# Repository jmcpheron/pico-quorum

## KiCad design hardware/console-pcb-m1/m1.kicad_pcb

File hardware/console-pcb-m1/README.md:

# M1 prototype console carrier

2026-10-07. Native KiCad schematic and routed PCB for the eight-button prototype.
The user chose an LCD module and a separate protected key adapter. The carrier
can now be quoted as a PCB assembly. It has not been built or bench-tested.

This version lives in `hardware/console-pcb-m1/`. Its CAD, local libraries,
fabrication exports and review drawings are kept together. Earlier concepts
remain in `hardware/console-pcb/`; they are separate versions.

- [Native schematic](m1.kicad_sch), [PCB](m1.kicad_pcb), [project](m1.kicad_pro).
- [Quote package](fab/m1-quote.zip), including Gerbers/drills, BOM, placement,
  schematic, assembly drawing, bare-board STEP, reports and file hashes.
- [Assembly and quote instructions](ASSEMBLY.md), including both harness pinouts.
- [Circuit drawing](review/m1.svg) and [placement drawing](review/placement.svg).

The carrier is 70 x 95 mm, two layers, with all 30 fitted parts on top. It has a
headerless Pico 2 W, eight SMT buttons, a JST PH LCD connector, 33R display series
resistors, local decoupling, host bus pull-ups, a default-off request pull-down,
four debug/service pads and eight internal key-adapter pads. Power comes from
the Pico's micro-USB socket. No battery or rotary control is included.

The display is Waveshare's 1.3inch LCD Module, SKU 15867, bought and mounted separately.
It uses a keyed harness rather than a soldered bare-panel ribbon. The adapter's
protection circuit is not on this board. Do not connect a USB-C plug or key directly
to the host pads. See ASSEMBLY.md for what that separate adapter must do.

The PCB's radio cutout and copper void follow the Pico module footprint. The main
board neck carries the traces around the antenna area. Keep the LCD, cable and
case hardware clear of that area. The screen envelope is an allowance: no enclosure
or complete assembly stack has been checked. The render uses the stock Pico W model
as a shape stand-in for Pico 2 W; the LCD and J1 connector body are not modelled.

## Checks completed

KiCad 10.0.6: ERC **0 errors / 0 warnings**; all-severity DRC **0 findings**;
unconnected items **0**; schematic/PCB parity **0**. No custom DRC exclusions were
added. The reports also list KiCad's default ignored checks. The export script
verifies that the 30 BOM references equal the placement references, and that all
are on the top side. Both checks passed.

Compared the Pico footprint, underside pads and stencil drawing with the maker's
PDF. Checked the switch's pad dimensions and internally common terminals. Checked
the JST PH family, pitch and header dimensions; the downloaded JST land-pattern
page could not be fully rendered because the local PDF reader lacks its font map.
The connector uses the stock KiCad footprint and still needs assembler drawing review.
Read the LCD's manual and circuit, including the backlight transistor and opposite
connector numbering. Inspected the exported schematic and PCB render.

Ran `git diff --check` and whitespace checks on new text files. Exported and checked
the Gerber/drill archive, BOM/CPL reference sets and file hashes. No firmware, web or
browser CI suites ran: this change is hardware CAD and supporting files only.
No installed dependency, board write, chip provisioning, lock, supplier quote or order.

Some local KiCad checks/rendering crashed in the filesystem sandbox. They completed
outside it. KiCad also logged a font-config notice; circuit/PCB checks completed.
PCB scripts use the existing key-board schematic helper and installed KiCad Python.
No dependency was added.

## Still to check

Assembler acceptance of the Pico module, stencil, JST footprint and parts sourcing;
LCD harness continuity and physical stack; button plungers and Sign recess; milled
cutout corner radii; Wi-Fi and supply behaviour under load; protected adapter design
and tests; Select/Device navigation and the existing review/reject/hold-to-sign checks.
Quote the carrier now, then resolve those before making or using a complete console.

`bootstrap.py` made the initial native files. It deliberately produces an unrouted
board and refuses to overwrite without `--force`. **Do not rerun it on this routed
design.** The native files are now the source. Regenerate exports with:

```sh
python3 hardware/console-pcb-m1/export.py
```

That command needs `kicad-cli`. STEP/rendering additionally use the installed KiCad
models. The `console_m1` symbol and footprint libraries are local to this project.
No change to the signing site, firmware image, ordered key-C board or release tags.

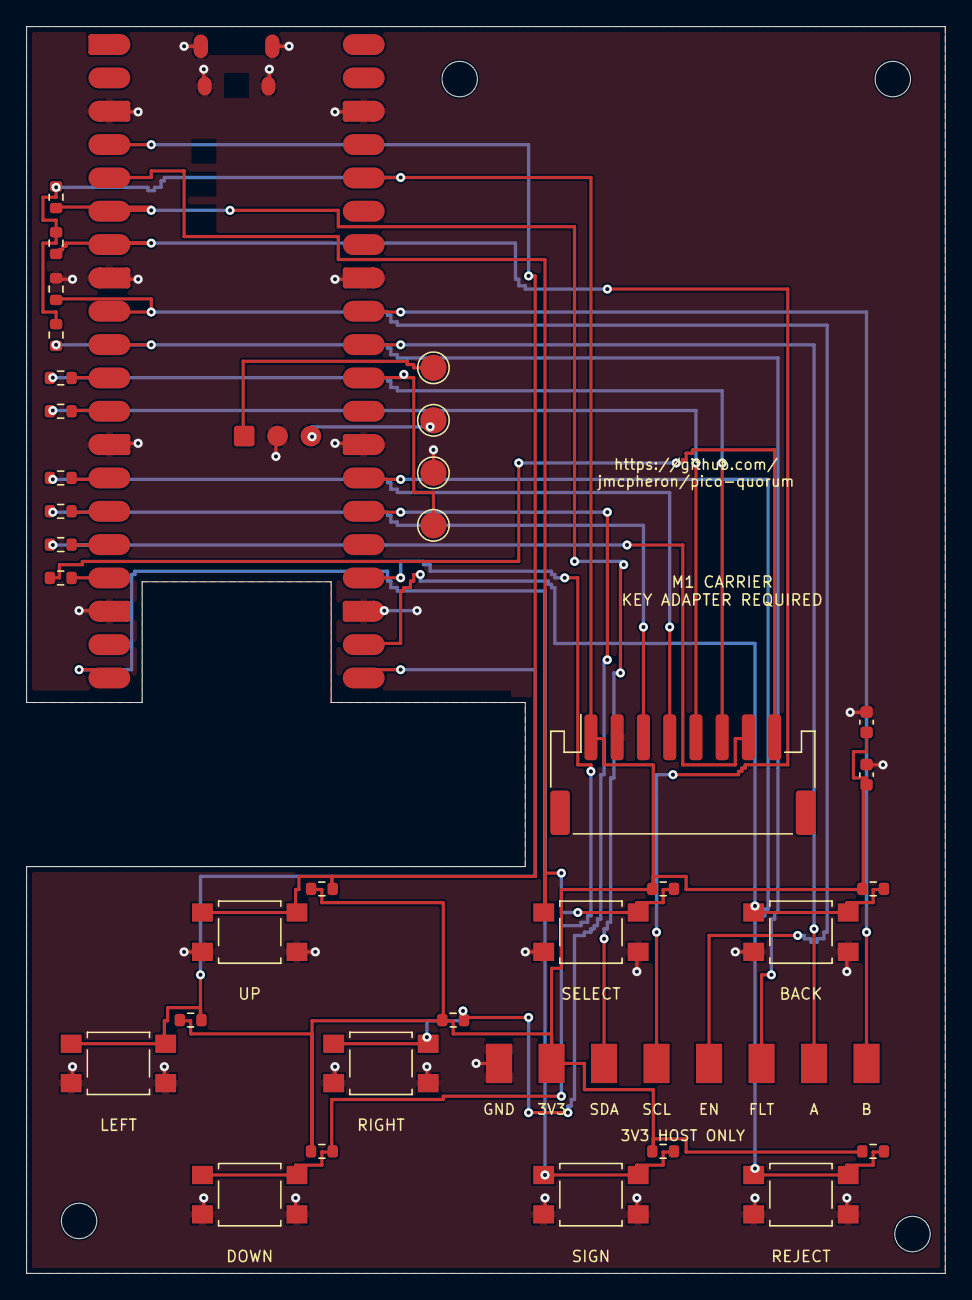
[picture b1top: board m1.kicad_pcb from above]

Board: 2 copper layers, 70.0 x 95.0 mm, 39 parts (0 on the bottom side), 31 nets.

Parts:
C1: 100n; C_0603_1608Metric
C2: 10u; C_0603_1608Metric
H1, H2, H3, H4: M2.5; MountingHole_2.7mm_M2.5
J1: S8B-PH-SM4-TB; JST_PH_S8B-PH-SM4-TB_1x08-1MP_P2.00mm_Horizontal
J2: INTERNAL ADAPTER PADS; AdapterPads8
R1, R2, R3, R4, R5, R6, R7, R8, R18: 10k; R_0603_1608Metric
R9, R10, R11, R12, R13, R14: 33R; R_0603_1608Metric
R15, R16: 2.2k; R_0603_1608Metric
R17: 100k; R_0603_1608Metric
SW1, SW2, SW3, SW4, SW5, SW6, SW7, SW8: TL3305AF160QG; SW_SPST_TL3305A
TP1: SWCLK; TestPoint_Pad_D2.0mm
TP2: SWDIO; TestPoint_Pad_D2.0mm
TP3: GND; TestPoint_Pad_D2.0mm
TP4: RUN; TestPoint_Pad_D2.0mm
U1: Pico 2 W; Pico2W_SMD

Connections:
/+3V3: C1.1, C2.1, J1.1, J2.2, R1.1, R2.1, R3.1, R4.1, R5.1, R6.1, R7.1, R8.1, R15.2, R16.2, R18.2, U1.36
/ATTACH_A: J2.7, U1.31
/ATTACH_B: J2.8, U1.32
/BTN_BACK: R6.2, SW6.1, U1.22
/BTN_DOWN: R2.2, SW2.1, U1.24
/BTN_LEFT: R3.2, SW3.1, U1.21
/BTN_REJECT: R8.2, SW8.1, U1.27
/BTN_RIGHT: R4.2, SW4.1, U1.26
/BTN_SELECT: R5.2, SW5.1, U1.5
/BTN_SIGN: R7.2, SW7.1, U1.20
/BTN_UP: R1.2, SW1.1, U1.4
/HOST_SCL: J2.4, R16.1, U1.7
/HOST_SDA: J2.3, R15.1, U1.6
/KEY_EN: J2.5, R17.1, U1.9
/KEY_FAULT: J2.6, R18.1, U1.10
/LCD_BL: J1.8, R14.2
/LCD_CS: J1.5, R11.2
/LCD_DC: J1.6, R12.2
/LCD_MOSI: J1.3, R9.2
/LCD_RST: J1.7, R13.2
/LCD_SCK: J1.4, R10.2
/MCU_BL: R14.1, U1.17
/MCU_CS: R11.1, U1.12
/MCU_DC: R12.1, U1.11
/MCU_MOSI: R9.1, U1.15
/MCU_RST: R13.1, U1.16
/MCU_SCK: R10.1, U1.14
/RUN: TP4.1, U1.30
/SWCLK: TP1.1, U1.D1
/SWDIO: TP2.1, U1.D3
GND: C1.2, C2.2, J1.2, J2.1, R17.2, SW1.2, SW2.2, SW3.2, SW4.2, SW5.2, SW6.2, SW7.2, SW8.2, TP3.1, U1.3, U1.8, U1.13, U1.18, U1.23, U1.28, U1.33, U1.38, U1.D2

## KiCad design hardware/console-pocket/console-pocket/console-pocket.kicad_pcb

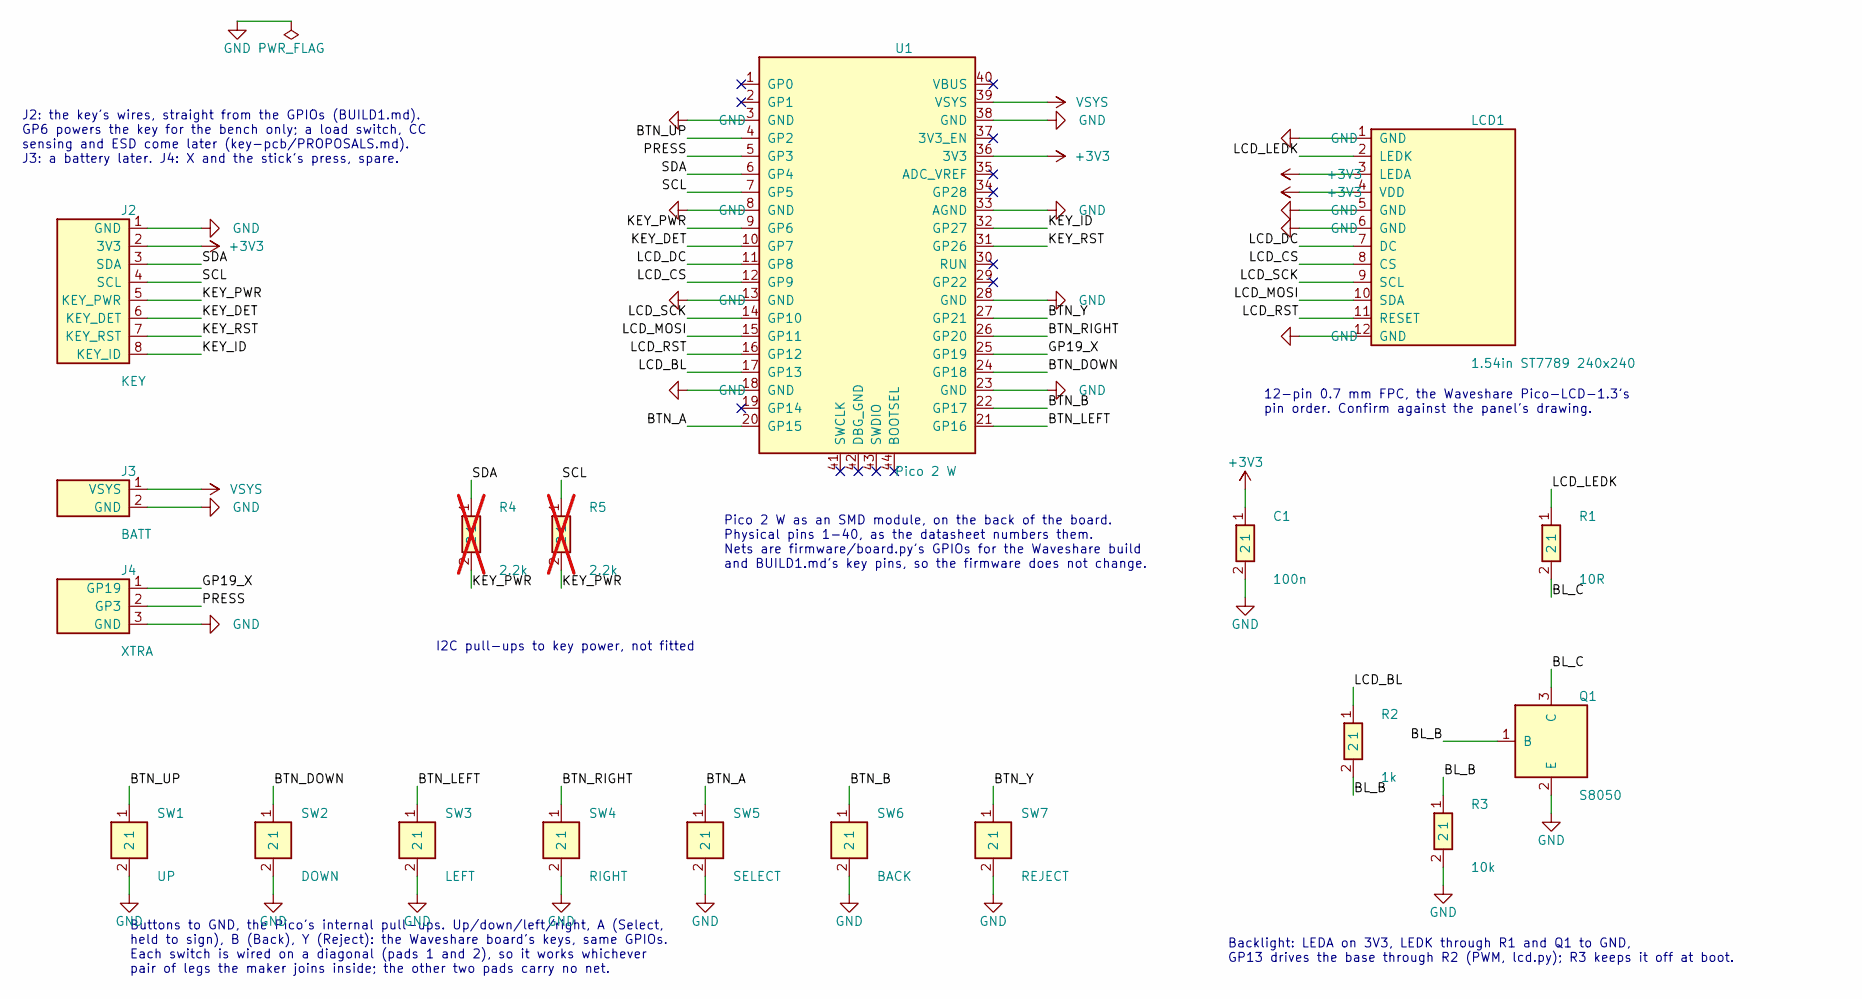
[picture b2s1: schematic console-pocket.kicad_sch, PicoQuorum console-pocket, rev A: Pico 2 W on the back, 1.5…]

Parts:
C1: 100n; C_0603; LCSC C14663
J2: KEY; Pads_1x8_P2.54mm
J3: BATT; Pads_1x2_P2.54mm
J4: XTRA; Pads_1x3_P2.54mm
LCD1: 1.54in ST7789 240x240; LCD_1.54in_240x240_FPC12_P0.7mm
Q1: S8050; SOT-23; MPN S8050 J3Y; LCSC C2150
R1: 10R; R_0603; LCSC C22859
R2: 1k; R_0603; LCSC C21190
R3: 10k; R_0603; LCSC C25804
R4, R5: 2.2k; R_0603; LCSC C4190; not fitted
SW1: UP; SW_SMD_6x6x5_TS1097A; MPN TS-1097A-05026; LCSC C720496
SW2: DOWN; SW_SMD_6x6x5_TS1097A; MPN TS-1097A-05026; LCSC C720496
SW3: LEFT; SW_SMD_6x6x5_TS1097A; MPN TS-1097A-05026; LCSC C720496
SW4: RIGHT; SW_SMD_6x6x5_TS1097A; MPN TS-1097A-05026; LCSC C720496
SW5: SELECT; SW_SMD_6x6x5_TS1097A; MPN TS-1097A-05026; LCSC C720496
SW6: BACK; SW_SMD_6x6x5_TS1097A; MPN TS-1097A-05026; LCSC C720496
SW7: REJECT; SW_SMD_6x6x5_TS1097A; MPN TS-1097A-05026; LCSC C720496
U1: Pico 2 W; Pico2W_SMD; MPN SC1633

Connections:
+3V3: C1.1, J2.2 (3V3), LCD1.3 (LEDA), LCD1.4 (VDD), U1.36 (3V3)
/BL_B: Q1.1 (B), R2.2, R3.1
/BL_C: Q1.3 (C), R1.2
/BTN_A: SW5.1, U1.20 (GP15)
/BTN_B: SW6.1, U1.22 (GP17)
/BTN_DOWN: SW2.1, U1.24 (GP18)
/BTN_LEFT: SW3.1, U1.21 (GP16)
/BTN_RIGHT: SW4.1, U1.26 (GP20)
/BTN_UP: SW1.1, U1.4 (GP2)
/BTN_Y: SW7.1, U1.27 (GP21)
/GP19_X: J4.1 (GP19), U1.25 (GP19)
/KEY_DET: J2.6 (KEY_DET), U1.10 (GP7)
/KEY_ID: J2.8 (KEY_ID), U1.32 (GP27)
/KEY_PWR: J2.5 (KEY_PWR), R4.2, R5.2, U1.9 (GP6)
/KEY_RST: J2.7 (KEY_RST), U1.31 (GP26)
/LCD_BL: R2.1, U1.17 (GP13)
/LCD_CS: LCD1.8 (CS), U1.12 (GP9)
/LCD_DC: LCD1.7 (DC), U1.11 (GP8)
/LCD_LEDK: LCD1.2 (LEDK), R1.1
/LCD_MOSI: LCD1.10 (SDA), U1.15 (GP11)
/LCD_RST: LCD1.11 (RESET), U1.16 (GP12)
/LCD_SCK: LCD1.9 (SCL), U1.14 (GP10)
/PRESS: J4.2 (GP3), U1.5 (GP3)
/SCL: J2.4 (SCL), R5.1, U1.7 (GP5)
/SDA: J2.3 (SDA), R4.1, U1.6 (GP4)
GND: C1.2, J2.1 (GND), J3.2 (GND), J4.3 (GND), LCD1.1 (GND), LCD1.5 (GND), LCD1.6 (GND), LCD1.12 (GND), Q1.2 (E), R3.2, SW1.2, SW2.2, SW3.2, SW4.2, SW5.2, SW6.2, SW7.2, U1.3 (GND), U1.8 (GND), U1.13 (GND), U1.18 (GND), U1.23 (GND), U1.28 (GND), U1.33 (AGND), U1.38 (GND)
VSYS: J3.1 (VSYS), U1.39 (VSYS)

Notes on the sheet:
Pico 2 W as an SMD module, on the back of the board. Physical pins 1-40, as the datasheet numbers them. Nets are firmware/board.py's GPIOs for the Waveshare build and BUILD1.md's key pins, so the firmware does not change.
Buttons to GND, the Pico's internal pull-ups. Up/down/left/right, A (Select, held to sign), B (Back), Y (Reject): the Waveshare board's keys, same GPIOs. Each switch is wired on a diagonal (pads 1 and 2), so it works whichever pair of legs the maker joins inside; the other two pads carry no net.
J2: the key's wires, straight from the GPIOs (BUILD1.md). GP6 powers the key for the bench only; a load switch, CC sensing and ESD come later (key-pcb/PROPOSALS.md). J3: a battery later. J4: X and the stick's press, spare.
I2C pull-ups to key power, not fitted
12-pin 0.7 mm FPC, the Waveshare Pico-LCD-1.3's pin order. Confirm against the panel's drawing.
Backlight: LEDA on 3V3, LEDK through R1 and Q1 to GND, GP13 drives the base through R2 (PWM, lcd.py); R3 keeps it off at boot.

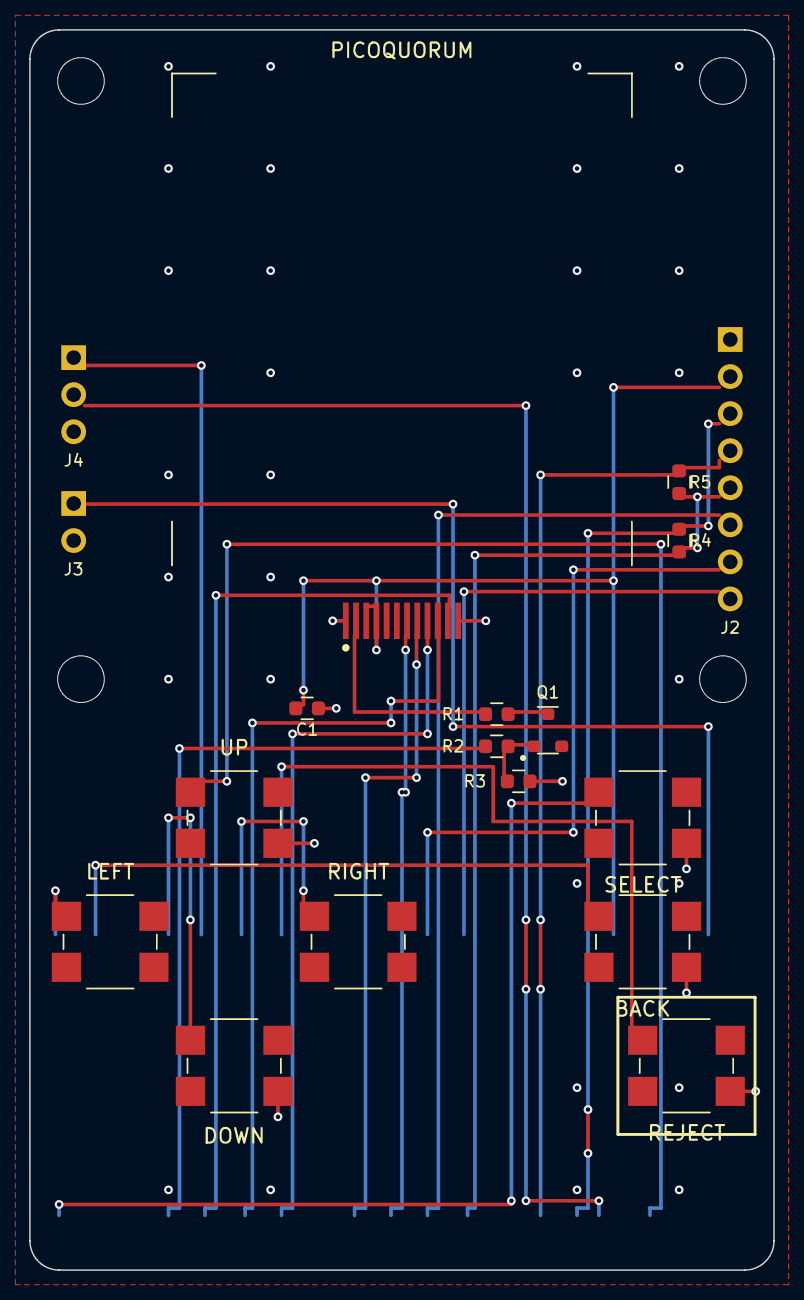
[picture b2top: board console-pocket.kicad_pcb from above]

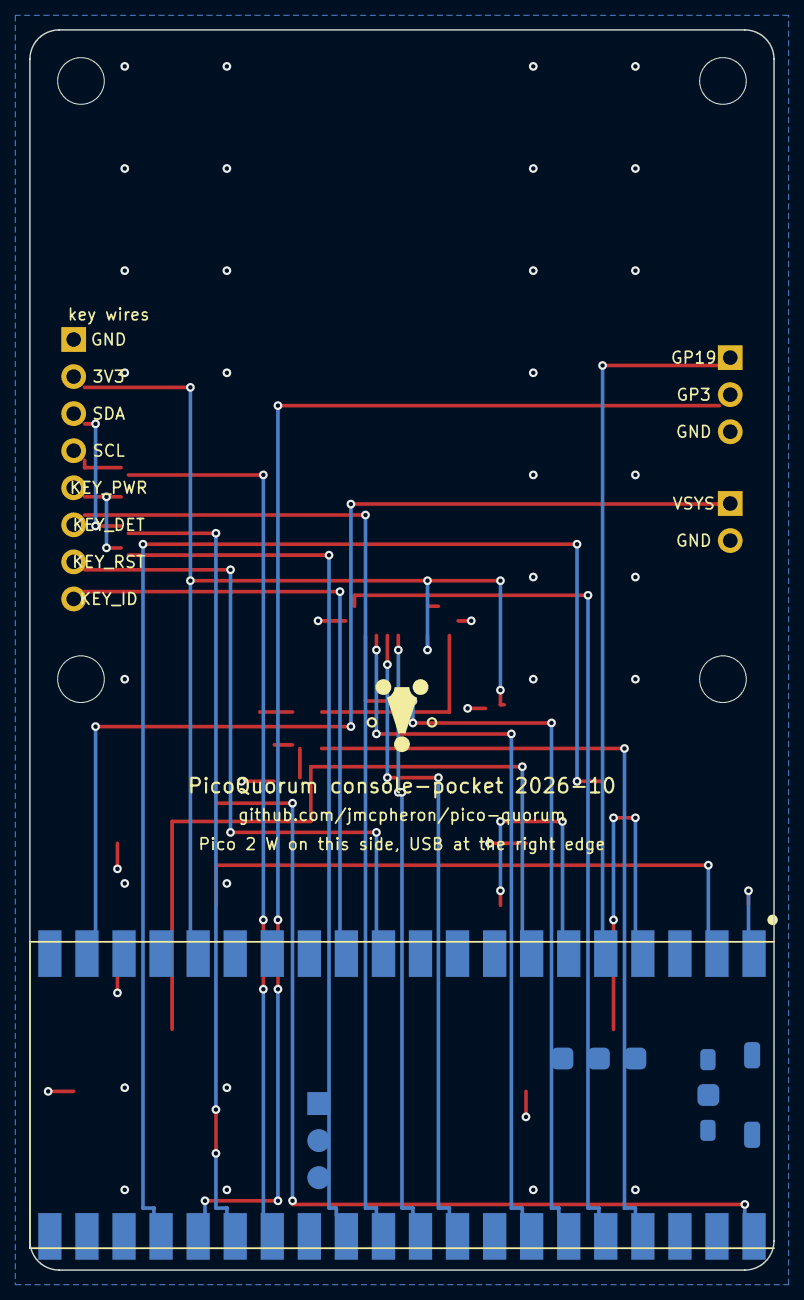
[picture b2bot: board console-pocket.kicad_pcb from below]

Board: 2 copper layers, 51.0 x 85.0 mm, 24 parts (2 on the bottom side), 27 nets.

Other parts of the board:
H1, H2, H3, H4: M3; MountingHole_3.2mm
LOGO1: PicoQuorum_Mark

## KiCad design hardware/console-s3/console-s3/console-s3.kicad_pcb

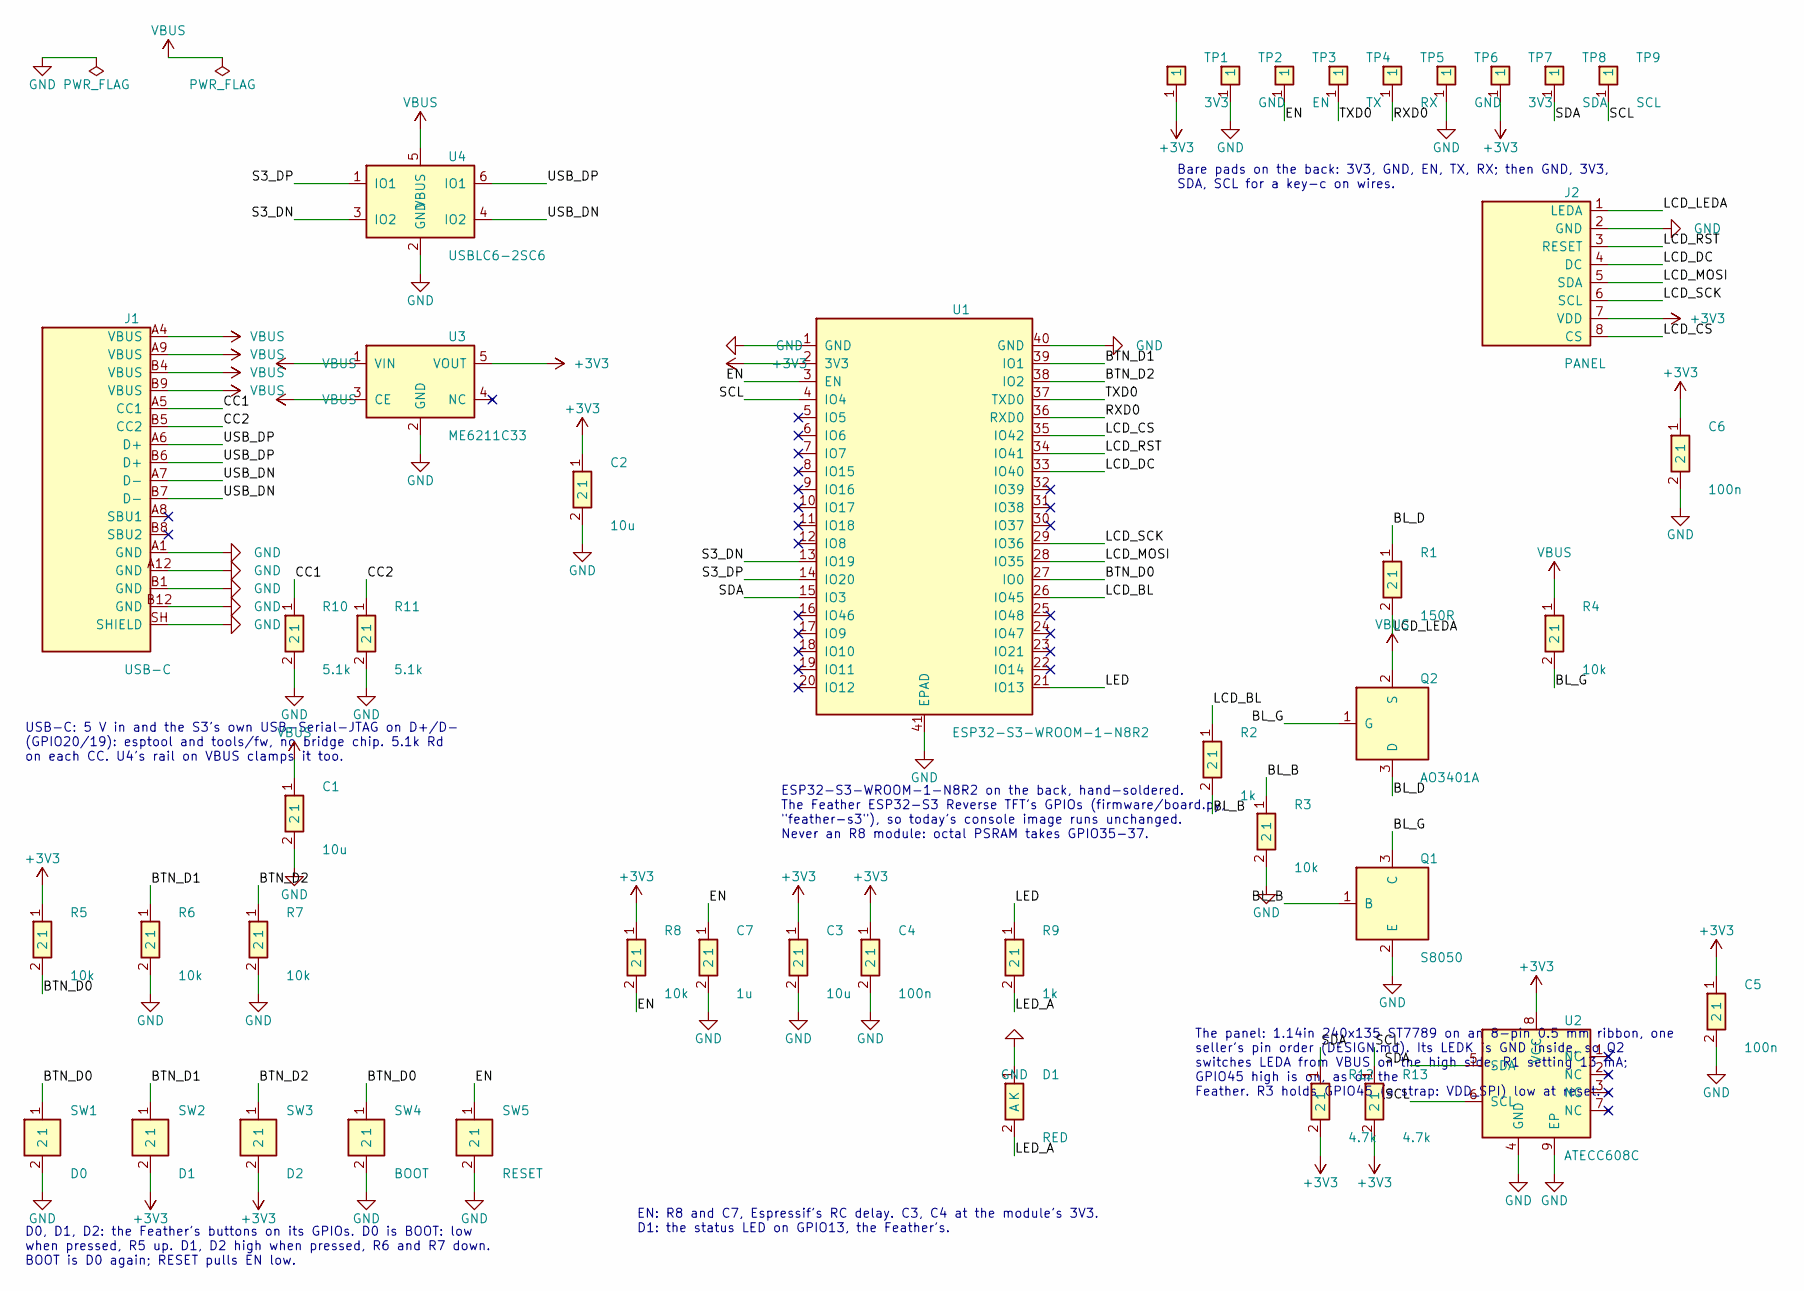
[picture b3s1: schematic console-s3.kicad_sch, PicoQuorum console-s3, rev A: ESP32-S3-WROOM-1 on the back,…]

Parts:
C1, C2, C3: 10u; C_0603; LCSC C19702
C4, C5, C6: 100n; C_0603; LCSC C14663
C7: 1u; C_0603; LCSC C15849
D1: RED; LED_0603; LCSC C2286
J1: USB-C; USB_C_Receptacle_HCTL_HC-TYPE-C-16P-01A; MPN HC-TYPE-C-16P-01A; LCSC C2894897
J2: PANEL; FPC_ZIF_8P_P0.5mm_HDGC_0.5K-HX-8PWB; MPN 0.5K-HX-8PWB; LCSC C2919492
Q1: S8050; SOT-23; MPN SS8050; LCSC C2150
Q2: AO3401A; SOT-23; MPN AO3401A; LCSC C15127
R1: 150R; R_0603; LCSC C22808
R2, R9: 1k; R_0603; LCSC C21190
R3, R4, R5, R6, R7, R8: 10k; R_0603; LCSC C25804
R10, R11: 5.1k; R_0603; LCSC C23186
R12, R13: 4.7k; R_0603; LCSC C23162
SW1: D0; SW_TS-1187A; MPN TS-1187A-B-A-B; LCSC C318884
SW2: D1; SW_TS-1187A; MPN TS-1187A-B-A-B; LCSC C318884
SW3: D2; SW_TS-1187A; MPN TS-1187A-B-A-B; LCSC C318884
SW4: BOOT; SW_TS-1187A; MPN TS-1187A-B-A-B; LCSC C318884
SW5: RESET; SW_TS-1187A; MPN TS-1187A-B-A-B; LCSC C318884
TP1, TP7: 3V3; TestPad_1.5mm_Back
TP2, TP6: GND; TestPad_1.5mm_Back
TP3: EN; TestPad_1.5mm_Back
TP4: TX; TestPad_1.5mm_Back
TP5: RX; TestPad_1.5mm_Back
TP8: SDA; TestPad_1.5mm_Back
TP9: SCL; TestPad_1.5mm_Back
U1: ESP32-S3-WROOM-1-N8R2; ESP32-S3-WROOM-1; MPN ESP32-S3-WROOM-1-N4R2
U2: ATECC608C; DFN-8-1EP_3x2mm_P0.5mm; MPN ATECC608C-MAHDA-S; LCSC C23291019
U3: ME6211C33; SOT-23-5; MPN ME6211C33M5G-N; LCSC C82942
U4: USBLC6-2SC6; SOT-23-6; MPN USBLC6-2SC6; LCSC C7519

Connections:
+3V3: C2.1, C3.1, C4.1, C5.1, C6.1, J2.7 (VDD), R5.1, R8.1, R12.2, R13.2, SW2.2, SW3.2, TP1.1, TP7.1, U1.2 (3V3), U2.8 (VCC), U3.5 (VOUT)
/BL_B: Q1.1 (B), R2.2, R3.1
/BL_D: Q2.3 (D), R1.1
/BL_G: Q1.3 (C), Q2.1 (G), R4.2
/BTN_D0: R5.2, SW1.1, SW4.1, U1.27 (IO0)
/BTN_D1: R6.1, SW2.1, U1.39 (IO1)
/BTN_D2: R7.1, SW3.1, U1.38 (IO2)
/CC1: J1.A5 (CC1), R10.1
/CC2: J1.B5 (CC2), R11.1
/EN: C7.1, R8.2, SW5.1, TP3.1, U1.3 (EN)
/LCD_BL: R2.1, U1.26 (IO45)
/LCD_CS: J2.8 (CS), U1.35 (IO42)
/LCD_DC: J2.4 (DC), U1.33 (IO40)
/LCD_LEDA: J2.1 (LEDA), R1.2
/LCD_MOSI: J2.5 (SDA), U1.28 (IO35)
/LCD_RST: J2.3 (RESET), U1.34 (IO41)
/LCD_SCK: J2.6 (SCL), U1.29 (IO36)
/LED: R9.1, U1.21 (IO13)
/LED_A: D1.2 (A), R9.2
/RXD0: TP5.1, U1.36 (RXD0)
/S3_DN: U1.13 (IO19), U4.3 (IO2)
/S3_DP: U1.14 (IO20), U4.1 (IO1)
/SCL: R13.1, TP9.1, U1.4 (IO4), U2.6 (SCL)
/SDA: R12.1, TP8.1, U1.15 (IO3), U2.5 (SDA)
/TXD0: TP4.1, U1.37 (TXD0)
/USB_DN: J1.A7 (D-), J1.B7 (D-), U4.4 (IO2)
/USB_DP: J1.A6 (D+), J1.B6 (D+), U4.6 (IO1)
GND: C1.2, C2.2, C3.2, C4.2, C5.2, C6.2, C7.2, D1.1 (K), J1.A1 (GND), J1.A12 (GND), J1.B1 (GND), J1.B12 (GND), J1.SH (SHIELD), J2.2 (GND), Q1.2 (E), R3.2, R6.2, R7.2, R10.2, R11.2, SW1.2, SW4.2, SW5.2, TP2.1, TP6.1, U1.1 (GND), U1.40 (GND), U1.41 (EPAD), U2.4 (GND), U2.9 (EP), U3.2 (GND), U4.2 (GND)
VBUS: C1.1, J1.A4 (VBUS), J1.A9 (VBUS), J1.B4 (VBUS), J1.B9 (VBUS), Q2.2 (S), R4.1, U3.1 (VIN), U3.3 (CE), U4.5 (VBUS)

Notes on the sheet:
ESP32-S3-WROOM-1-N8R2 on the back, hand-soldered. The Feather ESP32-S3 Reverse TFT's GPIOs (firmware/board.py, "feather-s3"), so today's console image runs unchanged. Never an R8 module: octal PSRAM takes GPIO35-37.
USB-C: 5 V in and the S3's own USB-Serial-JTAG on D+/D- (GPIO20/19): esptool and tools/fw, no bridge chip. 5.1k Rd on each CC. U4's rail on VBUS clamps it too.
The panel: 1.14in 240x135 ST7789 on an 8-pin 0.5 mm ribbon, one seller's pin order (DESIGN.md). Its LEDK is GND inside, so Q2 switches LEDA from VBUS on the high side, R1 setting 13 mA; GPIO45 high is on, as on the Feather. R3 holds GPIO45 (a strap: VDD_SPI) low at reset.
D0, D1, D2: the Feather's buttons on its GPIOs. D0 is BOOT: low when pressed, R5 up. D1, D2 high when pressed, R6 and R7 down. BOOT is D0 again; RESET pulls EN low.
EN: R8 and C7, Espressif's RC delay. C3, C4 at the module's 3V3. D1: the status LED on GPIO13, the Feather's.
Bare pads on the back: 3V3, GND, EN, TX, RX; then GND, 3V3, SDA, SCL for a key-c on wires.

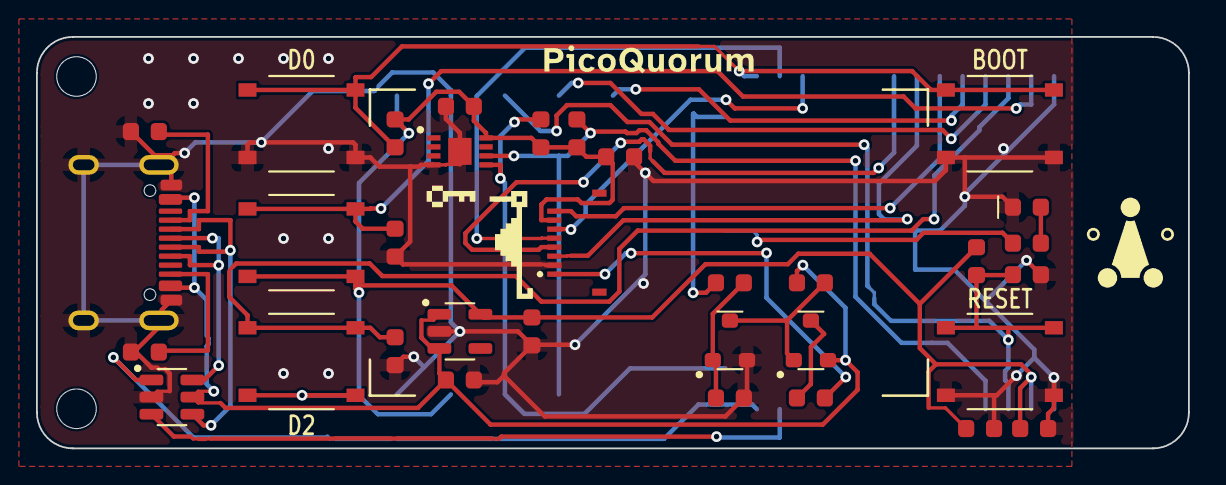
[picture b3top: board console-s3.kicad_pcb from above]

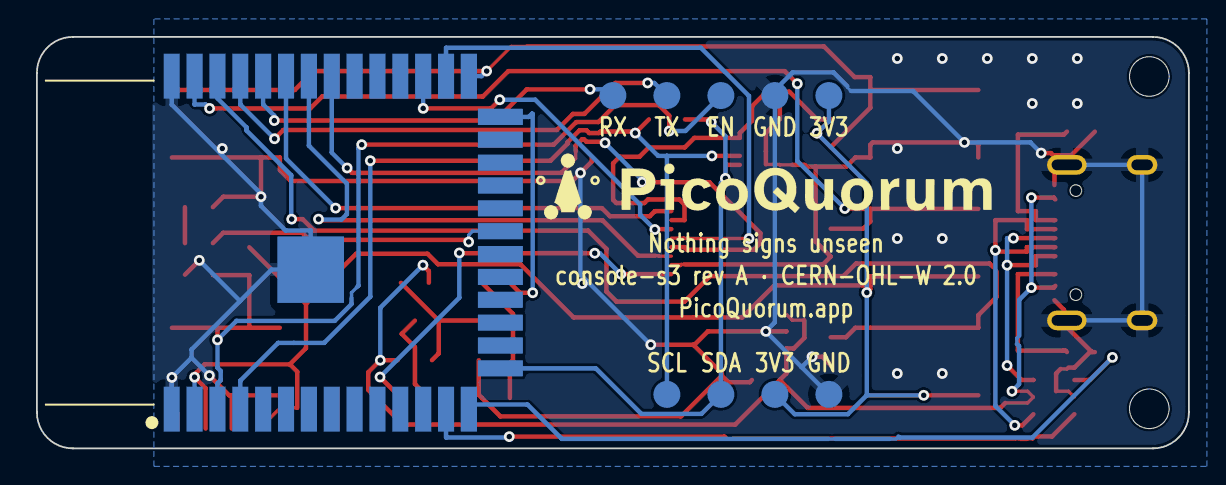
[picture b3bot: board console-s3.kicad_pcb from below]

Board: 2 copper layers, 64.0 x 22.9 mm, 45 parts (10 on the bottom side), 29 nets.

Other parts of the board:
H1, H2: M2; MountingHole_2.2mm

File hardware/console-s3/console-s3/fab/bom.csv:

Comment,Designator,Footprint,LCSC Part #
10u,"C1,C2,C3",C_0603,C19702
100n,"C4,C5,C6",C_0603,C14663
1u,C7,C_0603,C15849
RED,D1,LED_0603,C2286
USB-C,J1,USB_C_Receptacle_HCTL_HC-TYPE-C-16P-01A,C2894897
PANEL,J2,FPC_ZIF_8P_P0.5mm_HDGC_0.5K-HX-8PWB,C2919492
S8050,Q1,SOT-23,C2150
AO3401A,Q2,SOT-23,C15127
150R,R1,R_0603,C22808
5.1k,"R10,R11",R_0603,C23186
4.7k,"R12,R13",R_0603,C23162
1k,"R2,R9",R_0603,C21190
10k,"R3,R4,R5,R6,R7,R8",R_0603,C25804
D0,SW1,SW_TS-1187A,C318884
D1,SW2,SW_TS-1187A,C318884
D2,SW3,SW_TS-1187A,C318884
BOOT,SW4,SW_TS-1187A,C318884
RESET,SW5,SW_TS-1187A,C318884
ATECC608C,U2,DFN-8-1EP_3x2mm_P0.5mm,C23291019
ME6211C33,U3,SOT-23-5,C82942
USBLC6-2SC6,U4,SOT-23-6,C7519

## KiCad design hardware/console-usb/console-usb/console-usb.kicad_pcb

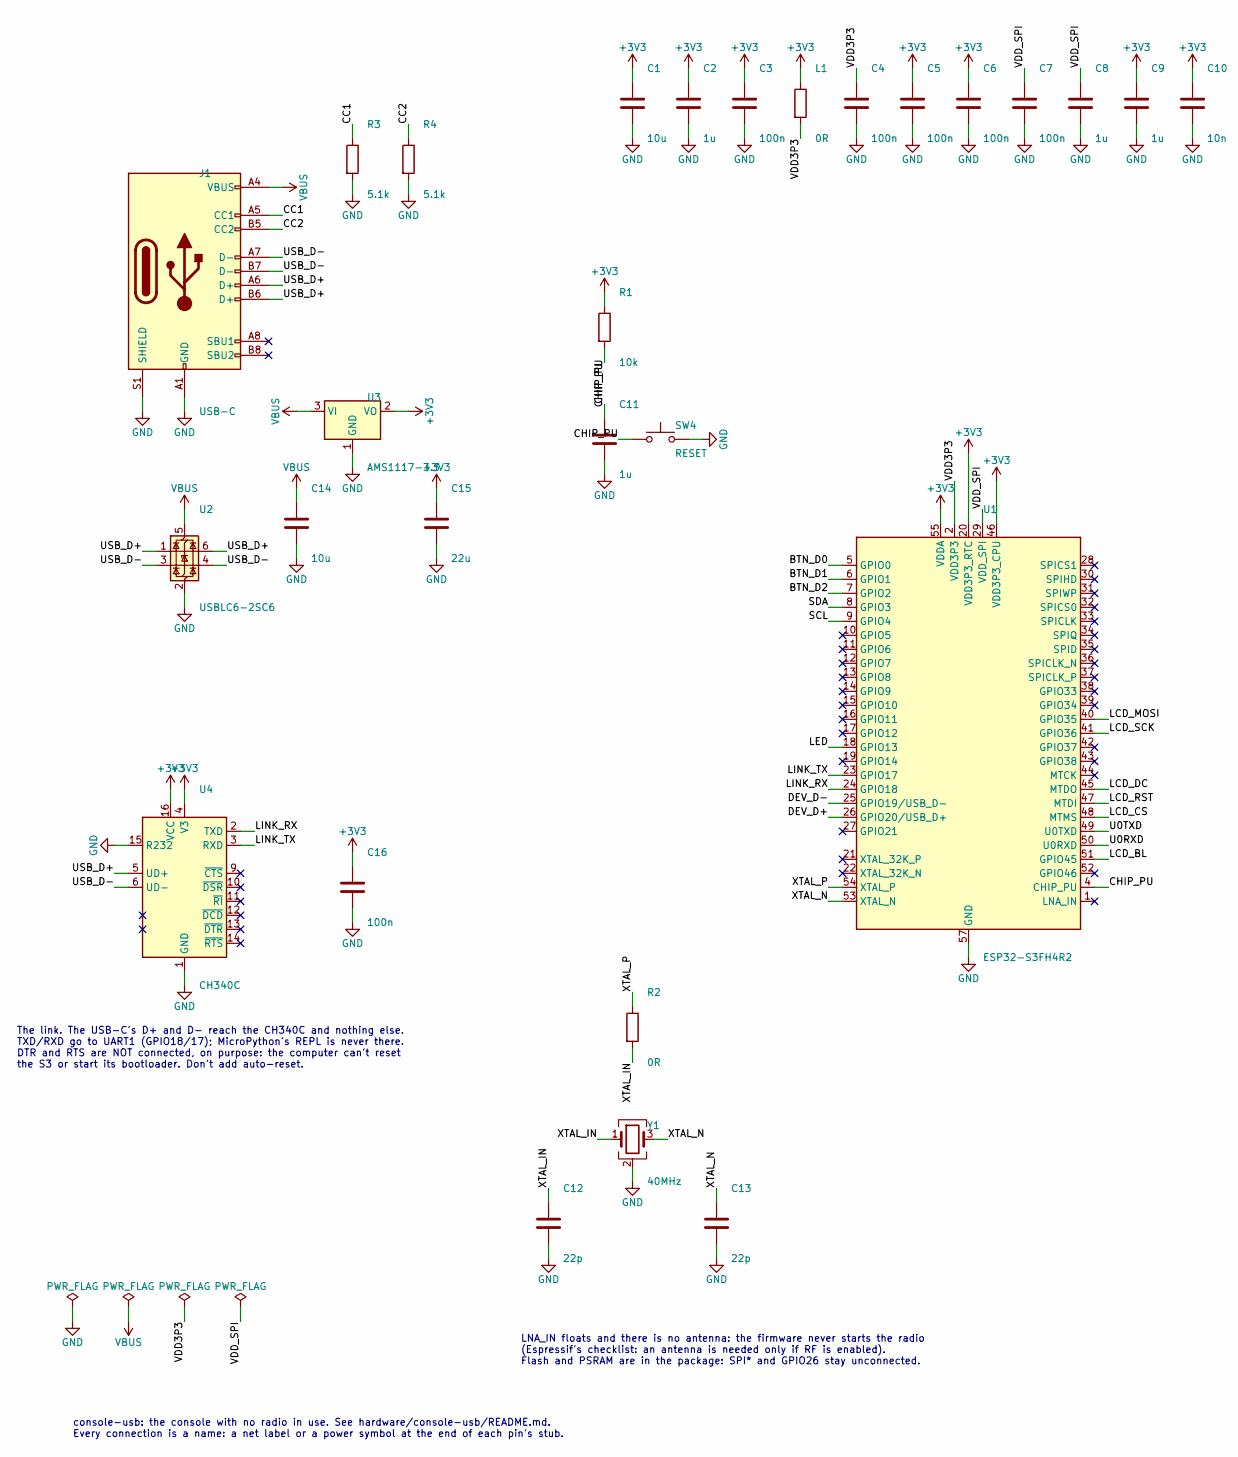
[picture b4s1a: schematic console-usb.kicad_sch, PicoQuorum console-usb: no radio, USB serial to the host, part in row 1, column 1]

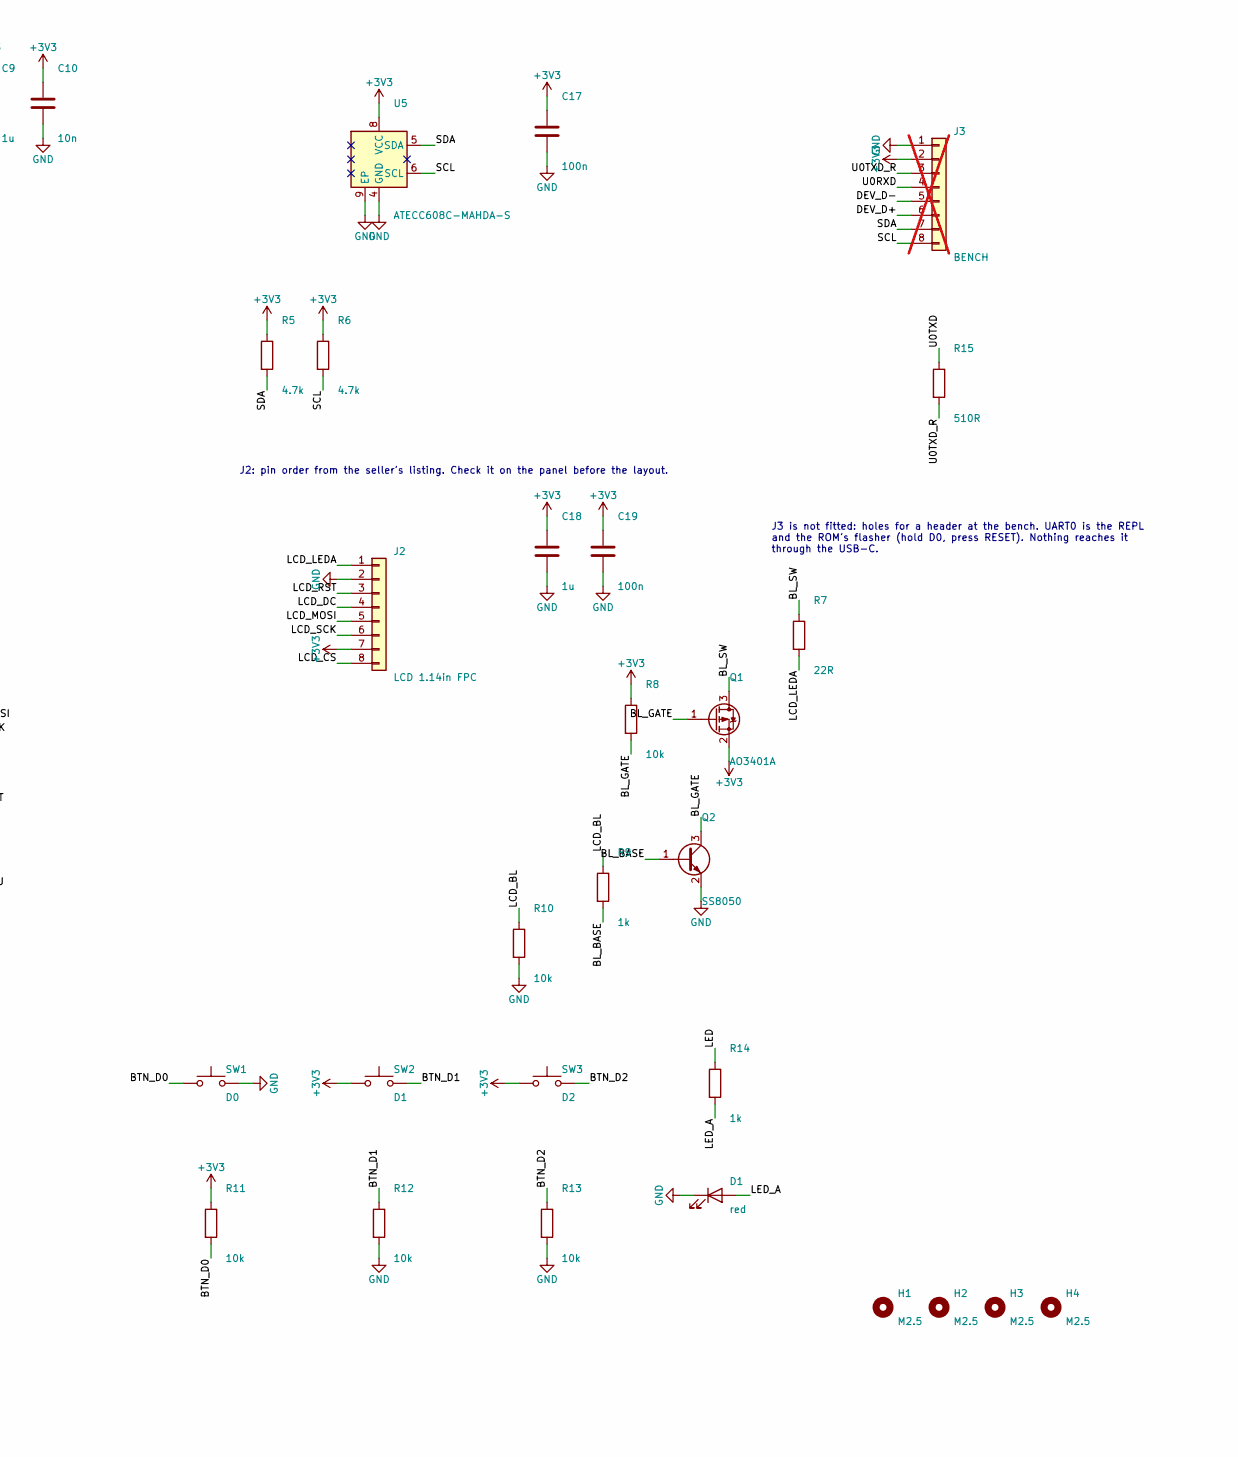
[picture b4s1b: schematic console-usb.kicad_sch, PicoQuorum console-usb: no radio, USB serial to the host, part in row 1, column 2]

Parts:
C1, C14: 10u; C_0805_2012Metric; LCSC C15850
C2, C8, C9, C11, C18: 1u; C_0402_1005Metric; LCSC C52923
C3, C4, C5, C6, C7, C16, C17, C19: 100n; C_0402_1005Metric; LCSC C1525
C10: 10n; C_0402_1005Metric; LCSC C15195
C12, C13: 22p; C_0402_1005Metric; LCSC C1555
C15: 22u; C_0805_2012Metric; LCSC C45783
D1: red; LED_0603_1608Metric; MPN KT-0603R; LCSC C2286
H1, H2, H3, H4: M2.5; MountingHole_2.7mm_M2.5
J1: USB-C; USB_C_Receptacle_HRO_TYPE-C-31-M-12; MPN TYPE-C-31-M-12; LCSC C165948
J2: LCD 1.14in FPC; FPC_ZIF_8P_P0.5mm_HDGC_0.5K-HX-8PWB; MPN 0.5K-HX-8PWB; LCSC C2919492
J3: BENCH; PinHeader_1x08_P2.54mm_Vertical; not fitted
L1: 0R; R_0402_1005Metric; LCSC C17168
Q1: AO3401A; SOT-23; LCSC C15127
Q2: SS8050; SOT-23; MPN SS8050; LCSC C2150
R1, R8, R10, R11, R12, R13: 10k; R_0402_1005Metric; LCSC C25744
R2: 0R; R_0402_1005Metric; LCSC C17168
R3, R4: 5.1k; R_0402_1005Metric; LCSC C25905
R5, R6: 4.7k; R_0402_1005Metric; LCSC C25900
R7: 22R; R_0402_1005Metric; LCSC C25092
R9, R14: 1k; R_0402_1005Metric; LCSC C11702
R15: 510R; R_0402_1005Metric; LCSC C25123
SW1: D0; SW_Push_1P1T_XKB_TS-1187A; MPN TS-1187A-B-A-B; LCSC C318884
SW2: D1; SW_Push_1P1T_XKB_TS-1187A; MPN TS-1187A-B-A-B; LCSC C318884
SW3: D2; SW_Push_1P1T_XKB_TS-1187A; MPN TS-1187A-B-A-B; LCSC C318884
SW4: RESET; SW_Push_1P1T_XKB_TS-1187A; MPN TS-1187A-B-A-B; LCSC C318884
U1: ESP32-S3FH4R2; QFN-56-1EP_7x7mm_P0.4mm_EP4x4mm; MPN ESP32-S3FH4R2; LCSC C3013940
U2: USBLC6-2SC6; SOT-23-6; LCSC C7519
U3: AMS1117-3.3; SOT-223-3_TabPin2; LCSC C6186
U4: CH340C; SOIC-16_3.9x9.9mm_P1.27mm; LCSC C84681
U5: ATECC608C-MAHDA-S; DFN-8-1EP_3x2mm_P0.5mm_EP1.3x1.5mm; MPN ATECC608C-MAHDA-S; LCSC C23291019
Y1: 40MHz; Crystal_SMD_3225-4Pin_3.2x2.5mm; MPN X322540MPB4SI; LCSC C9010

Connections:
+3V3: C1.1, C2.1, C3.1, C5.1, C6.1, C9.1, C10.1, C15.1, C16.1, C17.1, C18.1, C19.1, J2.7, J3.2, L1.1, Q1.2 (S), R1.1, R5.1, R6.1, R8.1, R11.1, SW2.1, SW3.1, U1.20 (VDD3P3_RTC), U1.46 (VDD3P3_CPU), U1.55 (VDDA), U1.56 (VDDA), U3.2 (VO), U4.4 (V3), U4.16 (VCC), U5.8 (VCC)
/BL_BASE: Q2.1 (B), R9.2
/BL_GATE: Q1.1 (G), Q2.3 (C), R8.2
/BL_SW: Q1.3 (D), R7.1
/BTN_D0: R11.2, SW1.1, U1.5 (GPIO0)
/BTN_D1: R12.1, SW2.2, U1.6 (GPIO1)
/BTN_D2: R13.1, SW3.2, U1.7 (GPIO2)
/CC1: J1.A5 (CC1), R3.1
/CC2: J1.B5 (CC2), R4.1
/CHIP_PU: C11.1, R1.2, SW4.1, U1.4 (CHIP_PU)
/DEV_D+: J3.6, U1.26 (GPIO20/USB_D+)
/DEV_D-: J3.5, U1.25 (GPIO19/USB_D-)
/LCD_BL: R9.1, R10.1, U1.51 (GPIO45)
/LCD_CS: J2.8, U1.48 (MTMS)
/LCD_DC: J2.4, U1.45 (MTDO)
/LCD_LEDA: J2.1, R7.2
/LCD_MOSI: J2.5, U1.40 (GPIO35)
/LCD_RST: J2.3, U1.47 (MTDI)
/LCD_SCK: J2.6, U1.41 (GPIO36)
/LED: R14.1, U1.18 (GPIO13)
/LED_A: D1.2 (A), R14.2
/LINK_RX: U1.24 (GPIO18), U4.2 (TXD)
/LINK_TX: U1.23 (GPIO17), U4.3 (RXD)
/SCL: J3.8, R6.2, U1.9 (GPIO4), U5.6 (SCL)
/SDA: J3.7, R5.2, U1.8 (GPIO3), U5.5 (SDA)
/U0RXD: J3.4, U1.50 (U0RXD)
/U0TXD: R15.1, U1.49 (U0TXD)
/U0TXD_R: J3.3, R15.2
/USB_D+: J1.A6 (D+), J1.B6 (D+), U2.1 (I/O1), U2.6 (I/O1), U4.5 (UD+)
/USB_D-: J1.A7 (D-), J1.B7 (D-), U2.3 (I/O2), U2.4 (I/O2), U4.6 (UD-)
/VDD3P3: C4.1, L1.2, U1.2 (VDD3P3), U1.3 (VDD3P3)
/VDD_SPI: C7.1, C8.1, U1.29 (VDD_SPI)
/XTAL_IN: C12.1, R2.2, Y1.1
/XTAL_N: C13.1, U1.53 (XTAL_N), Y1.3
/XTAL_P: R2.1, U1.54 (XTAL_P)
GND: C1.2, C2.2, C3.2, C4.2, C5.2, C6.2, C7.2, C8.2, C9.2, C10.2, C11.2, C12.2, C13.2, C14.2, C15.2, C16.2, C17.2, C18.2, C19.2, D1.1 (K), J1.A1 (GND), J1.A12 (GND), J1.B1 (GND), J1.B12 (GND), J1.S1 (SHIELD), J2.2, J3.1, Q2.2 (E), R3.2, R4.2, R10.2, R12.2, R13.2, SW1.2, SW4.2, U1.57 (GND), U2.2 (GND), U3.1 (GND), U4.1 (GND), U4.15 (R232), U5.4 (GND), U5.9 (EP), Y1.2 (G), Y1.4 (G)
VBUS: C14.1, J1.A4 (VBUS), J1.A9 (VBUS), J1.B4 (VBUS), J1.B9 (VBUS), U2.5 (VBUS), U3.3 (VI)

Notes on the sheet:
console-usb: the console with no radio in use. See hardware/console-usb/README.md. Every connection is a name: a net label or a power symbol at the end of each pin's stub.
The link. The USB-C's D+ and D- reach the CH340C and nothing else. TXD/RXD go to UART1 (GPIO18/17); MicroPython's REPL is never there. DTR and RTS are NOT connected, on purpose: the computer can't reset the S3 or start its bootloader. Don't add auto-reset.
LNA_IN floats and there is no antenna: the firmware never starts the radio (Espressif's checklist: an antenna is needed only if RF is enabled). Flash and PSRAM are in the package: SPI* and GPIO26 stay unconnected.
J2: pin order from the seller's listing. Check it on the panel before the layout.
J3 is not fitted: holes for a header at the bench. UART0 is the REPL and the ROM's flasher (hold D0, press RESET). Nothing reaches it through the USB-C.

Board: 2 copper layers, 57 parts (1 on the bottom side), 37 nets, no tracks yet.

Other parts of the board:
LCD1: 1.14in 240x135; LCD_1.14in_240x135_on_tape
LOGO1: PicoQuorum_Mark

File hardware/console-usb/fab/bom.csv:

Comment,Designator,Footprint,LCSC Part #
10u,"C1,C14",C_0805_2012Metric,C15850
1u,"C2,C8,C9,C11,C18",C_0402_1005Metric,C52923
100n,"C3,C4,C5,C6,C7,C16,C17,C19",C_0402_1005Metric,C1525
10n,C10,C_0402_1005Metric,C15195
22p,"C12,C13",C_0402_1005Metric,C1555
22u,C15,C_0805_2012Metric,C45783
red,D1,LED_0603_1608Metric,C2286
USB-C,J1,USB_C_Receptacle_HRO_TYPE-C-31-M-12,C165948
LCD 1.14in FPC,J2,Hirose_FH12-8S-0.5SH_1x08-1MP_P0.50mm_Horizontal,C597995
0R,"L1,R2",R_0402_1005Metric,C17168
AO3401A,Q1,SOT-23,C15127
SS8050,Q2,SOT-23,C2150
10k,"R1,R8,R10,R11,R12,R13",R_0402_1005Metric,C25744
5.1k,"R3,R4",R_0402_1005Metric,C25905
4.7k,"R5,R6",R_0402_1005Metric,C25900
22R,R7,R_0402_1005Metric,C25092
1k,"R9,R14",R_0402_1005Metric,C11702
510R,R15,R_0402_1005Metric,C25123
D0,SW1,SW_Push_1P1T_XKB_TS-1187A,C318884
D1,SW2,SW_Push_1P1T_XKB_TS-1187A,C318884
D2,SW3,SW_Push_1P1T_XKB_TS-1187A,C318884
RESET,SW4,SW_Push_1P1T_XKB_TS-1187A,C318884
ESP32-S3FH4R2,U1,QFN-56-1EP_7x7mm_P0.4mm_EP4x4mm_ThermalVias,C3013940
USBLC6-2SC6,U2,SOT-23-6,C7519
AMS1117-3.3,U3,SOT-223-3_TabPin2,C6186
CH340C,U4,SOIC-16_3.9x9.9mm_P1.27mm,C84681
ATECC608C-MAHDA-S,U5,DFN-8-1EP_3x2mm_P0.5mm_EP1.3x1.5mm,C23291019
40MHz,Y1,Crystal_SMD_3225-4Pin_3.2x2.5mm,C9010

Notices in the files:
hardware/console-s3/console-s3/console-s3.kicad_pcb:
console-s3 rev A · CERN-OHL-W 2.0
hardware/console-usb/console-usb/console-usb.kicad_pcb:
CERN-OHL-W v2, Source Location as 4.1
hardware/console-usb/console-usb/console-usb.kicad_sch:
Written by hardware/console-usb/gen_console_usb.py. CERN-OHL-W v2
hardware/feather-wing/wing-a/wing-a.kicad_pcb:
CERN-OHL-W-2.0
